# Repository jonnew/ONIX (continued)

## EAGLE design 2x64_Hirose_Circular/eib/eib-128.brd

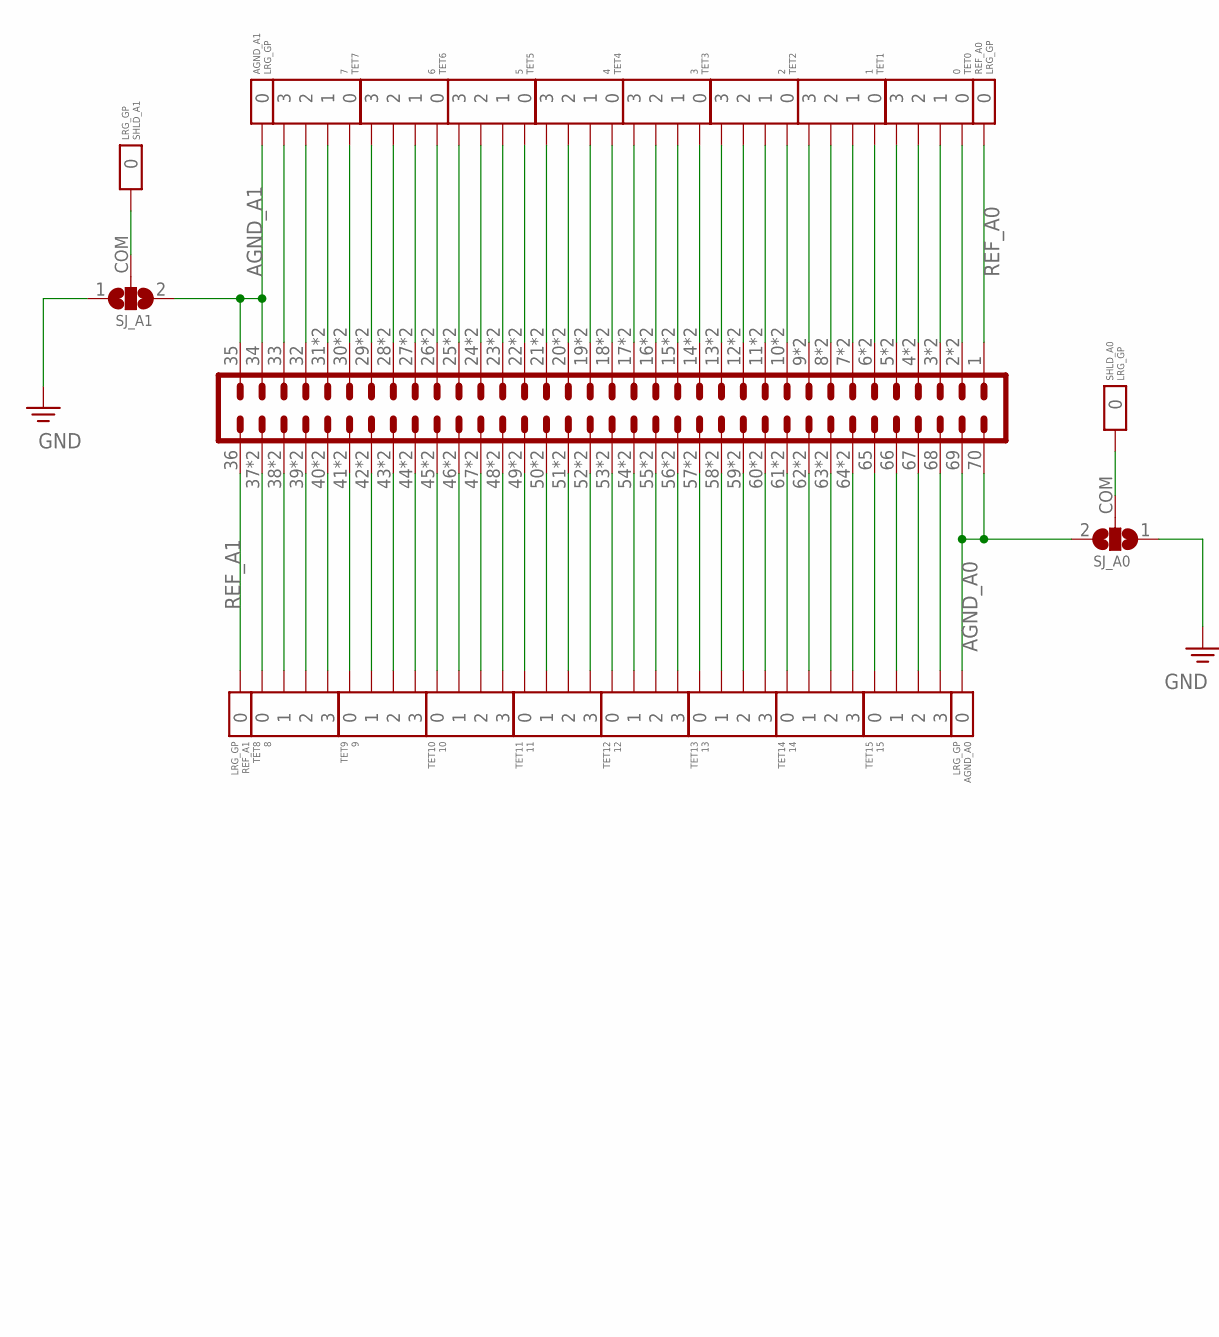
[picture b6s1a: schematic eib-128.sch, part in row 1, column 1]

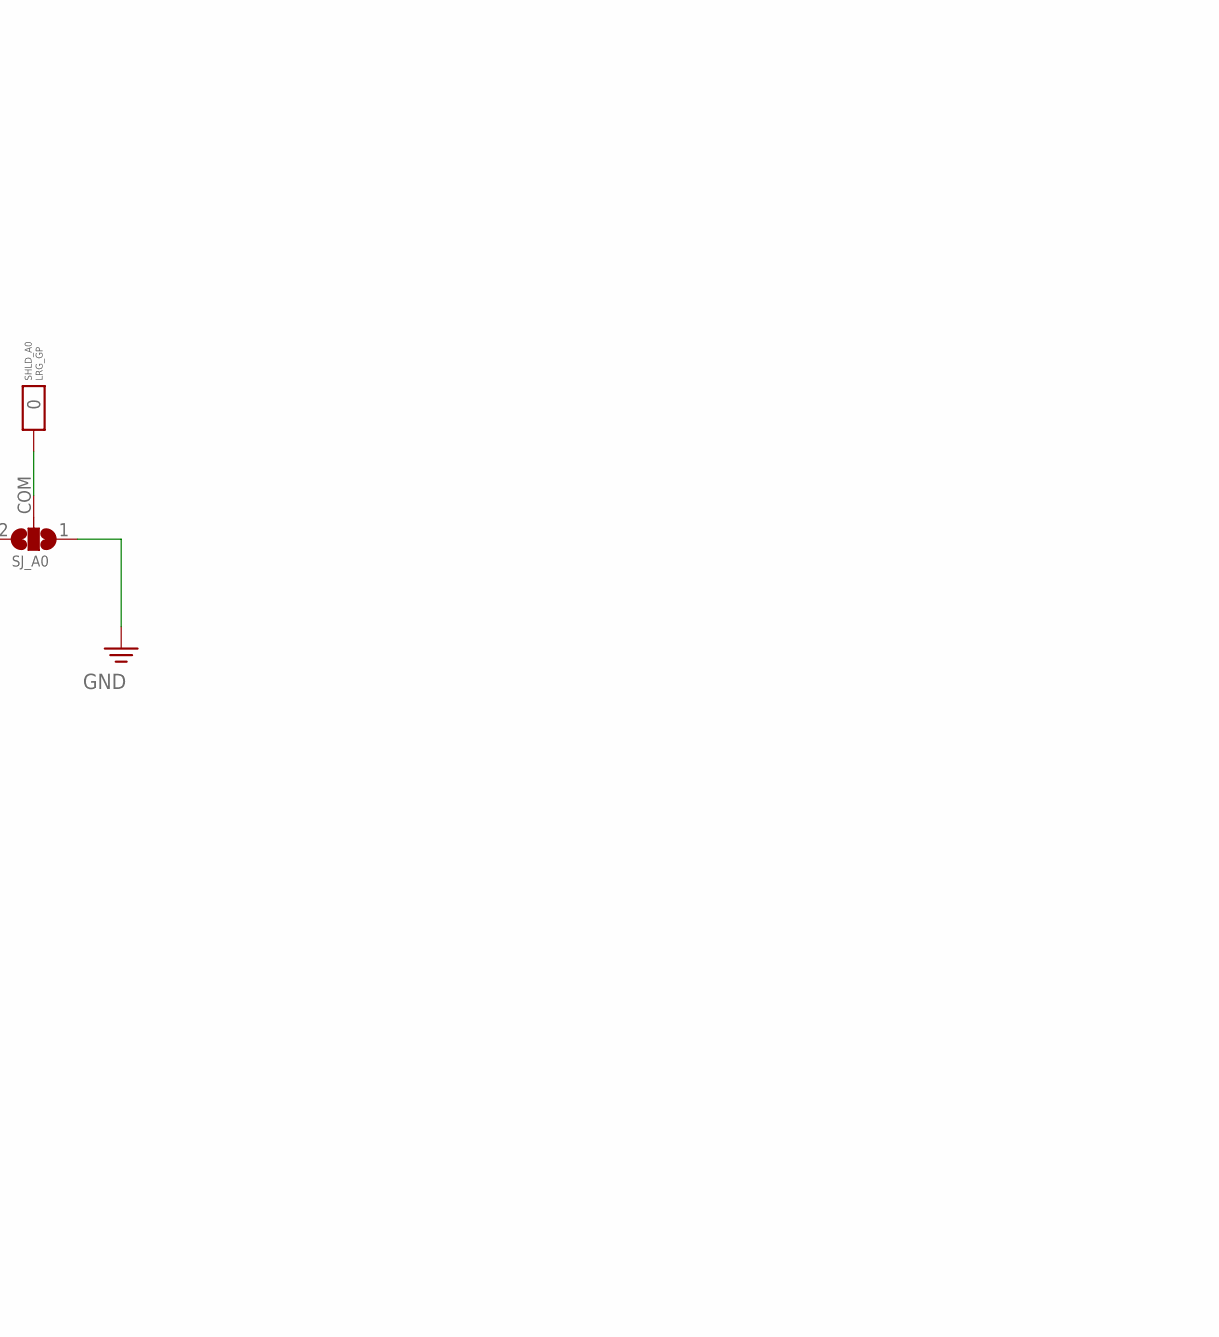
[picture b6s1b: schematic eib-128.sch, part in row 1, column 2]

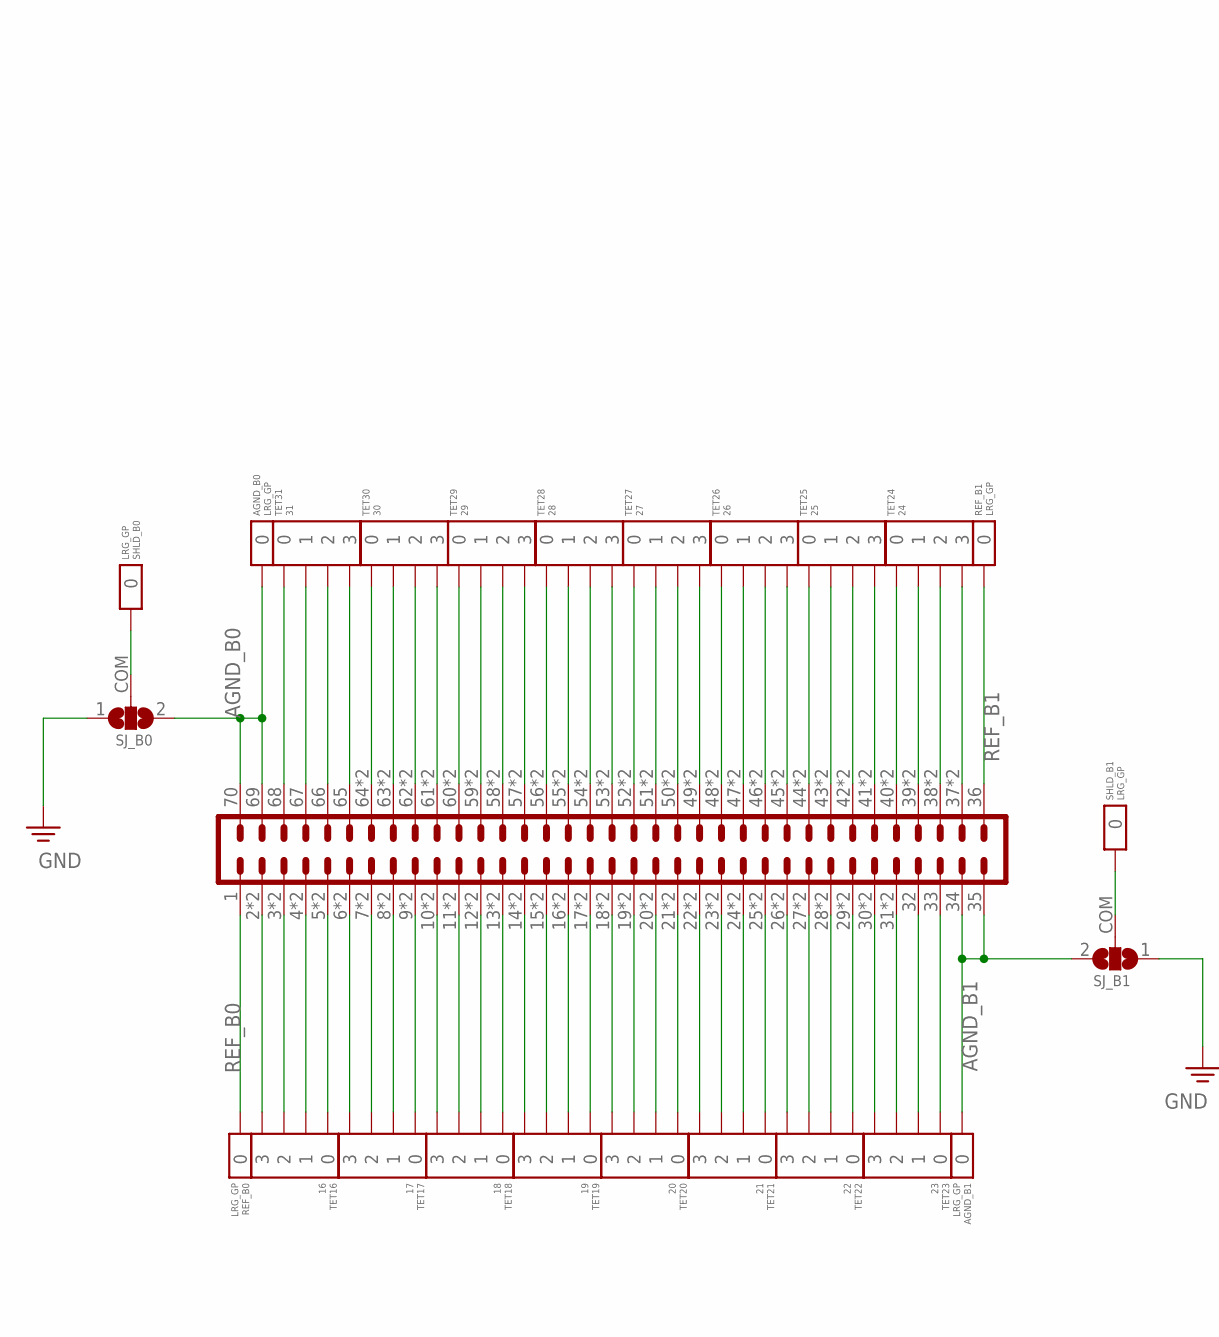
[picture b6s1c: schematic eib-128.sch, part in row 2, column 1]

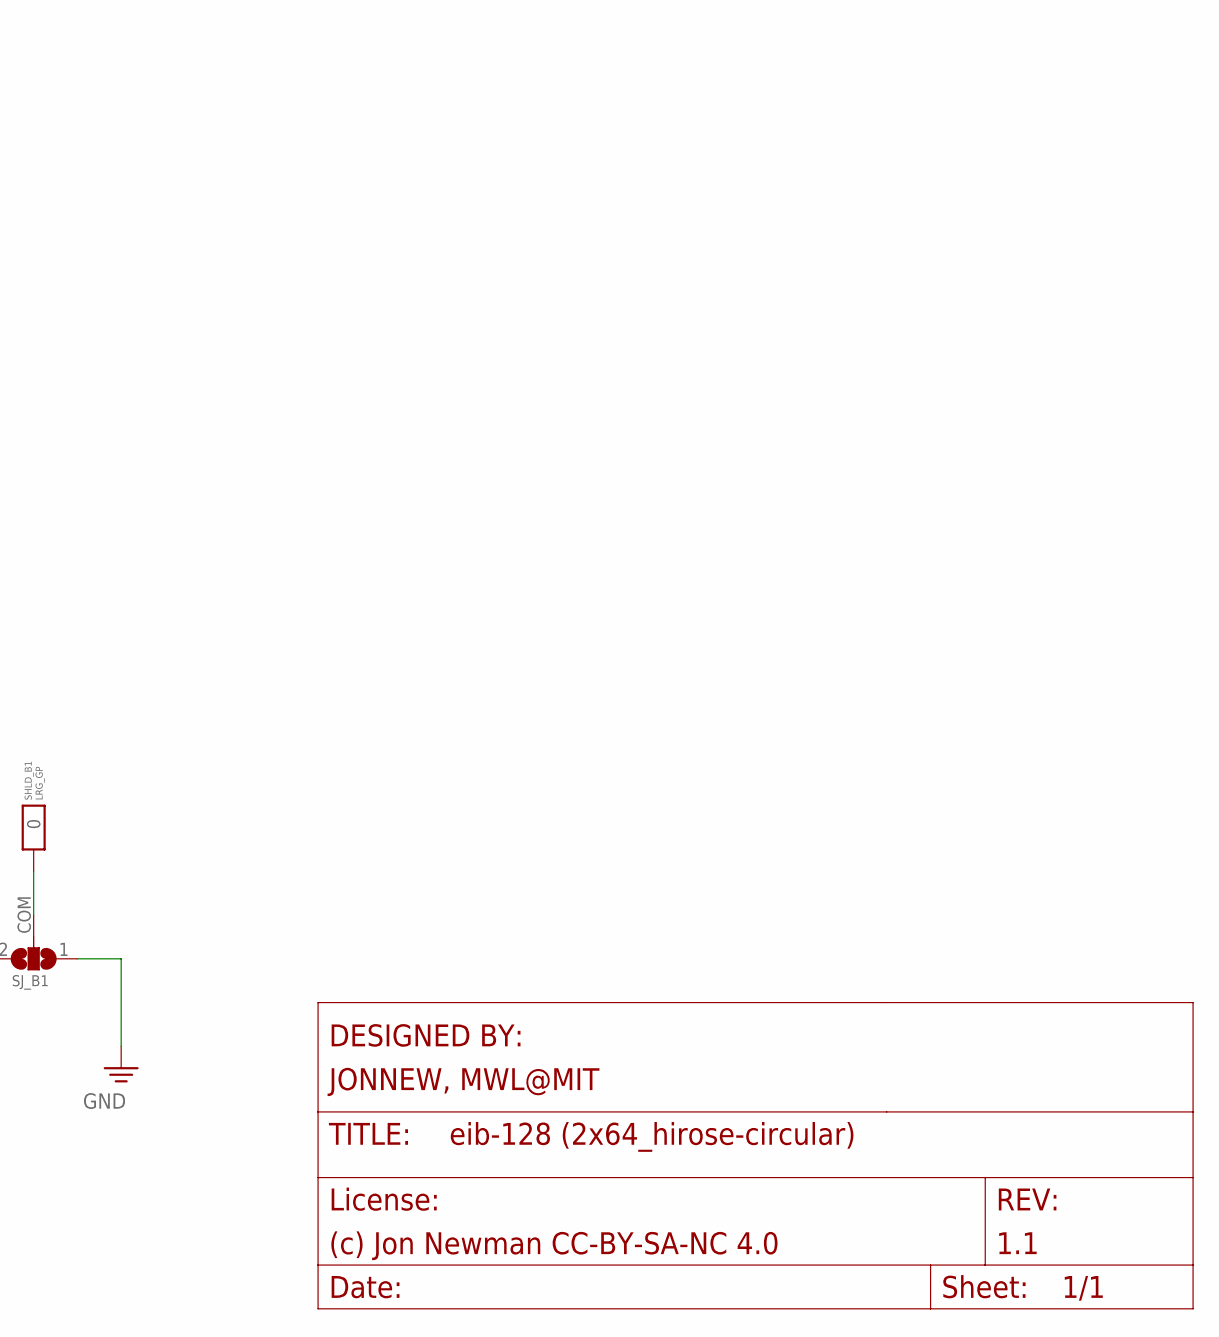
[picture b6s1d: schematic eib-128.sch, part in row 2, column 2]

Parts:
AGND_A0, AGND_A1: LRG_GP; GOLDPIN_0.5ID_0.7OD
AGND_B0, AGND_B1: LRG_GP; GOLDPIN_0.5ID_0.7OD
AIN_N0T: DF40HEAD; DF40-70HEAD-EIB
AIN_S0T: DF40HEAD; DF40-70HEAD-EIB
REF_A0, REF_A1: LRG_GP; GOLDPIN_0.5ID_0.7OD
REF_B0, REF_B1: LRG_GP; GOLDPIN_0.5ID_0.7OD
SHLD_A0, SHLD_A1: LRG_GP; GOLDPIN_0.5ID_0.7OD
SHLD_B0, SHLD_B1: LRG_GP; GOLDPIN_0.5ID_0.7OD
SJ_A0, SJ_A1: SJ2_0402; SJ_2_0402
SJ_B0, SJ_B1: SJ2_0402; SJ_2_0402
TET0: 0; TETRODE_128_0.5ID_0.7OD
TET1: 1; TETRODE_128_0.5ID_0.7OD
TET2: 2; TETRODE_128_0.5ID_0.7OD
TET3: 3; TETRODE_128_0.5ID_0.7OD
TET4: 4; TETRODE_128_0.5ID_0.7OD
TET5: 5; TETRODE_128_0.5ID_0.7OD
TET6: 6; TETRODE_128_0.5ID_0.7OD
TET7: 7; TETRODE_128_0.5ID_0.7OD
TET8: 8; TETRODE_128_0.5ID_0.7OD
TET9: 9; TETRODE_128_0.5ID_0.7OD
TET10: 10; TETRODE_128_0.5ID_0.7OD
TET11: 11; TETRODE_128_0.5ID_0.7OD
TET12: 12; TETRODE_128_0.5ID_0.7OD
TET13: 13; TETRODE_128_0.5ID_0.7OD
TET14: 14; TETRODE_128_0.5ID_0.7OD
TET15: 15; TETRODE_128_0.5ID_0.7OD
TET16: 16; TETRODE_128_0.5ID_0.7OD
TET17: 17; TETRODE_128_0.5ID_0.7OD
TET18: 18; TETRODE_128_0.5ID_0.7OD
TET19: 19; TETRODE_128_0.5ID_0.7OD
TET20: 20; TETRODE_128_0.5ID_0.7OD
TET21: 21; TETRODE_128_0.5ID_0.7OD
TET22: 22; TETRODE_128_0.5ID_0.7OD
TET23: 23; TETRODE_128_0.5ID_0.7OD
TET24: 24; TETRODE_128_0.5ID_0.7OD
TET25: 25; TETRODE_128_0.5ID_0.7OD
TET26: 26; TETRODE_128_0.5ID_0.7OD
TET27: 27; TETRODE_128_0.5ID_0.7OD
TET28: 28; TETRODE_128_0.5ID_0.7OD
TET29: 29; TETRODE_128_0.5ID_0.7OD
TET30: 30; TETRODE_128_0.5ID_0.7OD
TET31: 31; TETRODE_128_0.5ID_0.7OD

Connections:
AGND_A0: AGND_A0.P$1, AIN_N0T.69, AIN_N0T.70, SJ_A0.2
AGND_A1: AGND_A1.P$1, AIN_N0T.34, AIN_N0T.35, SJ_A1.2
AGND_B0: AGND_B0.P$1, AIN_S0T.69, AIN_S0T.70, SJ_B0.2
AGND_B1: AGND_B1.P$1, AIN_S0T.34, AIN_S0T.35, SJ_B1.2
GND: SJ_A0.1, SJ_A1.1, SJ_B0.1, SJ_B1.1
unnamed: SHLD_A0.P$1, SJ_A0.COM
unnamed: SHLD_A1.P$1, SJ_A1.COM
unnamed: SHLD_B0.P$1, SJ_B0.COM
unnamed: SHLD_B1.P$1, SJ_B1.COM
unnamed: AIN_S0T.33, TET23.0
unnamed: AIN_S0T.32, TET23.1
unnamed: AIN_S0T.31, AIN_S0T.P31 (31), TET23.2
unnamed: AIN_S0T.30, AIN_S0T.P30 (30), TET23.3
unnamed: AIN_S0T.29, AIN_S0T.P29 (29), TET22.0
unnamed: AIN_S0T.28, AIN_S0T.P28 (28), TET22.1
unnamed: AIN_S0T.27, AIN_S0T.P27 (27), TET22.2
unnamed: AIN_S0T.26, AIN_S0T.P26 (26), TET22.3
unnamed: AIN_S0T.25, AIN_S0T.P25 (25), TET21.0
unnamed: AIN_S0T.24, AIN_S0T.P24 (24), TET21.1
unnamed: AIN_S0T.23, AIN_S0T.P23 (23), TET21.2
unnamed: AIN_S0T.22, AIN_S0T.P22 (22), TET21.3
unnamed: AIN_S0T.21, AIN_S0T.P21 (21), TET20.0
unnamed: AIN_S0T.20, AIN_S0T.P20 (20), TET20.1
unnamed: AIN_S0T.19, AIN_S0T.P19 (19), TET20.2
unnamed: AIN_S0T.18, AIN_S0T.P18 (18), TET20.3
unnamed: AIN_S0T.17, AIN_S0T.P17 (17), TET19.0
unnamed: AIN_S0T.16, AIN_S0T.P16 (16), TET19.1
unnamed: AIN_S0T.15, AIN_S0T.P15 (15), TET19.2
unnamed: AIN_S0T.14, AIN_S0T.P14 (14), TET19.3
unnamed: AIN_S0T.13, AIN_S0T.P13 (13), TET18.0
unnamed: AIN_S0T.12, AIN_S0T.P12 (12), TET18.1
unnamed: AIN_S0T.11, AIN_S0T.P11 (11), TET18.2
unnamed: AIN_S0T.10, AIN_S0T.P10 (10), TET18.3
unnamed: AIN_S0T.9, AIN_S0T.P9 (9), TET17.0
unnamed: AIN_S0T.8, AIN_S0T.P8 (8), TET17.1
unnamed: AIN_S0T.7, AIN_S0T.P7 (7), TET17.2
unnamed: AIN_S0T.6, AIN_S0T.P6 (6), TET17.3
unnamed: AIN_S0T.5, AIN_S0T.P5 (5), TET16.0
unnamed: AIN_S0T.4, AIN_S0T.P4 (4), TET16.1
unnamed: AIN_S0T.3, AIN_S0T.P3 (3), TET16.2
unnamed: AIN_S0T.38, AIN_S0T.P38 (38), TET24.2
unnamed: AIN_S0T.39, AIN_S0T.P39 (39), TET24.1
unnamed: AIN_S0T.40, AIN_S0T.P40 (40), TET24.0
unnamed: AIN_S0T.41, AIN_S0T.P41 (41), TET25.3
unnamed: AIN_S0T.42, AIN_S0T.P42 (42), TET25.2
unnamed: AIN_S0T.43, AIN_S0T.P43 (43), TET25.1
unnamed: AIN_S0T.44, AIN_S0T.P44 (44), TET25.0
unnamed: AIN_S0T.45, AIN_S0T.P45 (45), TET26.3
unnamed: AIN_S0T.46, AIN_S0T.P46 (46), TET26.2
unnamed: AIN_S0T.47, AIN_S0T.P47 (47), TET26.1
unnamed: AIN_S0T.48, AIN_S0T.P48 (48), TET26.0
unnamed: AIN_S0T.49, AIN_S0T.P49 (49), TET27.3
unnamed: AIN_S0T.50, AIN_S0T.P50 (50), TET27.2
unnamed: AIN_S0T.51, AIN_S0T.P51 (51), TET27.1
unnamed: AIN_S0T.52, AIN_S0T.P52 (52), TET27.0
unnamed: AIN_S0T.53, AIN_S0T.P53 (53), TET28.3
unnamed: AIN_S0T.54, AIN_S0T.P54 (54), TET28.2
unnamed: AIN_S0T.55, AIN_S0T.P55 (55), TET28.1
unnamed: AIN_S0T.56, AIN_S0T.P56 (56), TET28.0
unnamed: AIN_S0T.57, AIN_S0T.P57 (57), TET29.3
unnamed: AIN_S0T.58, AIN_S0T.P58 (58), TET29.2
unnamed: AIN_S0T.59, AIN_S0T.P59 (59), TET29.1
unnamed: AIN_S0T.60, AIN_S0T.P60 (60), TET29.0
unnamed: AIN_S0T.61, AIN_S0T.P61 (61), TET30.3
unnamed: AIN_S0T.62, AIN_S0T.P62 (62), TET30.2
unnamed: AIN_S0T.63, AIN_S0T.P63 (63), TET30.1
unnamed: AIN_S0T.64, AIN_S0T.P64 (64), TET30.0
unnamed: AIN_S0T.65, TET31.3
unnamed: AIN_S0T.66, TET31.2
unnamed: AIN_S0T.67, TET31.1
unnamed: AIN_S0T.68, TET31.0
unnamed: AIN_S0T.2, AIN_S0T.P2 (2), TET16.3
unnamed: AIN_S0T.37, AIN_S0T.P37 (37), TET24.3
unnamed: AIN_N0T.33, TET7.3
unnamed: AIN_N0T.32, TET7.2
unnamed: AIN_N0T.31, AIN_N0T.P31 (31), TET7.1
unnamed: AIN_N0T.30, AIN_N0T.P30 (30), TET7.0
unnamed: AIN_N0T.29, AIN_N0T.P29 (29), TET6.3
unnamed: AIN_N0T.28, AIN_N0T.P28 (28), TET6.2
unnamed: AIN_N0T.27, AIN_N0T.P27 (27), TET6.1
unnamed: AIN_N0T.26, AIN_N0T.P26 (26), TET6.0
unnamed: AIN_N0T.25, AIN_N0T.P25 (25), TET5.3
unnamed: AIN_N0T.24, AIN_N0T.P24 (24), TET5.2
unnamed: AIN_N0T.23, AIN_N0T.P23 (23), TET5.1
unnamed: AIN_N0T.22, AIN_N0T.P22 (22), TET5.0
unnamed: AIN_N0T.21, AIN_N0T.P21 (21), TET4.3
unnamed: AIN_N0T.20, AIN_N0T.P20 (20), TET4.2
unnamed: AIN_N0T.19, AIN_N0T.P19 (19), TET4.1
unnamed: AIN_N0T.18, AIN_N0T.P18 (18), TET4.0
unnamed: AIN_N0T.17, AIN_N0T.P17 (17), TET3.3
unnamed: AIN_N0T.16, AIN_N0T.P16 (16), TET3.2
unnamed: AIN_N0T.15, AIN_N0T.P15 (15), TET3.1
unnamed: AIN_N0T.14, AIN_N0T.P14 (14), TET3.0
unnamed: AIN_N0T.13, AIN_N0T.P13 (13), TET2.3
unnamed: AIN_N0T.12, AIN_N0T.P12 (12), TET2.2
unnamed: AIN_N0T.11, AIN_N0T.P11 (11), TET2.1
unnamed: AIN_N0T.10, AIN_N0T.P10 (10), TET2.0
unnamed: AIN_N0T.9, AIN_N0T.P9 (9), TET1.3
unnamed: AIN_N0T.8, AIN_N0T.P8 (8), TET1.2
unnamed: AIN_N0T.7, AIN_N0T.P7 (7), TET1.1
unnamed: AIN_N0T.6, AIN_N0T.P6 (6), TET1.0
unnamed: AIN_N0T.5, AIN_N0T.P5 (5), TET0.3
unnamed: AIN_N0T.4, AIN_N0T.P4 (4), TET0.2
unnamed: AIN_N0T.3, AIN_N0T.P3 (3), TET0.1
unnamed: AIN_N0T.2, AIN_N0T.P2 (2), TET0.0
unnamed: AIN_N0T.38, AIN_N0T.P38 (38), TET8.1
unnamed: AIN_N0T.39, AIN_N0T.P39 (39), TET8.2
unnamed: AIN_N0T.40, AIN_N0T.P40 (40), TET8.3
unnamed: AIN_N0T.41, AIN_N0T.P41 (41), TET9.0
unnamed: AIN_N0T.42, AIN_N0T.P42 (42), TET9.1
unnamed: AIN_N0T.43, AIN_N0T.P43 (43), TET9.2
unnamed: AIN_N0T.44, AIN_N0T.P44 (44), TET9.3
unnamed: AIN_N0T.45, AIN_N0T.P45 (45), TET10.0
unnamed: AIN_N0T.46, AIN_N0T.P46 (46), TET10.1
unnamed: AIN_N0T.47, AIN_N0T.P47 (47), TET10.2
unnamed: AIN_N0T.48, AIN_N0T.P48 (48), TET10.3
unnamed: AIN_N0T.49, AIN_N0T.P49 (49), TET11.0
unnamed: AIN_N0T.50, AIN_N0T.P50 (50), TET11.1
unnamed: AIN_N0T.51, AIN_N0T.P51 (51), TET11.2
unnamed: AIN_N0T.52, AIN_N0T.P52 (52), TET11.3
unnamed: AIN_N0T.53, AIN_N0T.P53 (53), TET12.0
unnamed: AIN_N0T.54, AIN_N0T.P54 (54), TET12.1
unnamed: AIN_N0T.55, AIN_N0T.P55 (55), TET12.2
unnamed: AIN_N0T.56, AIN_N0T.P56 (56), TET12.3
unnamed: AIN_N0T.57, AIN_N0T.P57 (57), TET13.0
unnamed: AIN_N0T.58, AIN_N0T.P58 (58), TET13.1
unnamed: AIN_N0T.59, AIN_N0T.P59 (59), TET13.2
unnamed: AIN_N0T.60, AIN_N0T.P60 (60), TET13.3
unnamed: AIN_N0T.61, AIN_N0T.P61 (61), TET14.0
unnamed: AIN_N0T.62, AIN_N0T.P62 (62), TET14.1
unnamed: AIN_N0T.63, AIN_N0T.P63 (63), TET14.2
unnamed: AIN_N0T.64, AIN_N0T.P64 (64), TET14.3
unnamed: AIN_N0T.65, TET15.0
unnamed: AIN_N0T.66, TET15.1
unnamed: AIN_N0T.67, TET15.2
unnamed: AIN_N0T.68, TET15.3
unnamed: AIN_N0T.37, AIN_N0T.P37 (37), TET8.0
REF_A0: AIN_N0T.1, REF_A0.P$1
REF_A1: AIN_N0T.36, REF_A1.P$1
REF_B0: AIN_S0T.1, REF_B0.P$1
REF_B1: AIN_S0T.36, REF_B1.P$1

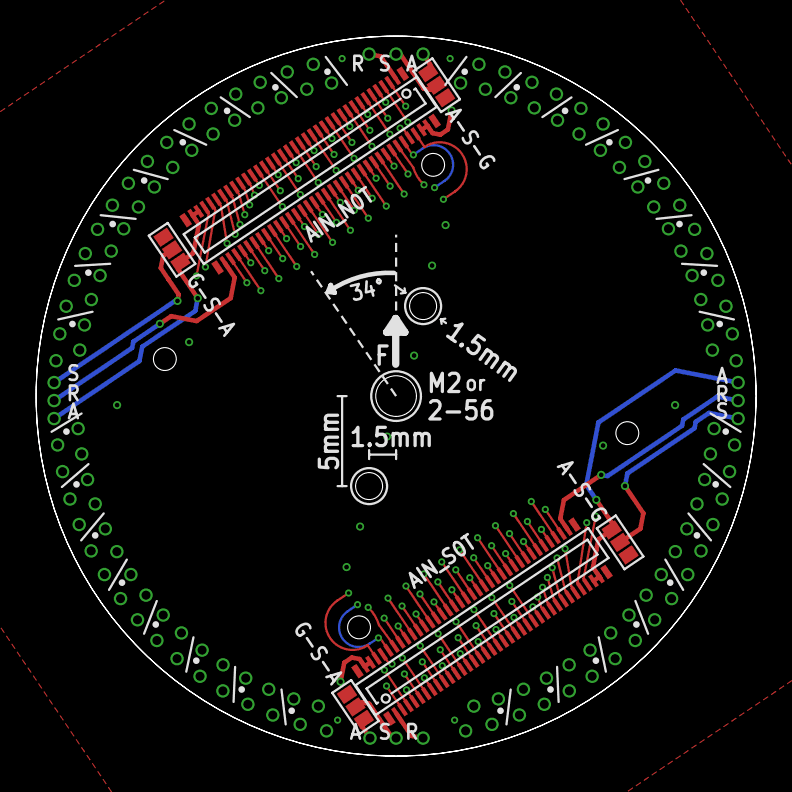
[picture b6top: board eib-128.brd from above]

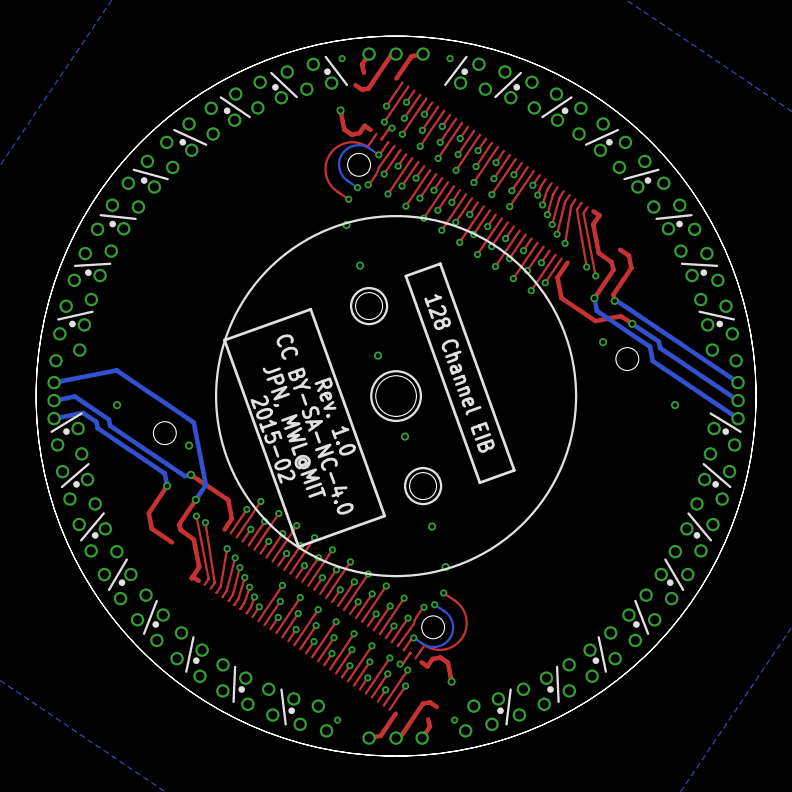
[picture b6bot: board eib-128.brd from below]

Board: 4 copper layers, 40.0 x 40.0 mm, 51 parts (16 on the bottom side), 141 nets.

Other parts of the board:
U$1: EIB_MOUNT_A
